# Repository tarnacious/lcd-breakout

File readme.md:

4 digit LCD Breakout board
==========================

This is a simple board to control a 4 digit reflexive LCD with three control
lines.

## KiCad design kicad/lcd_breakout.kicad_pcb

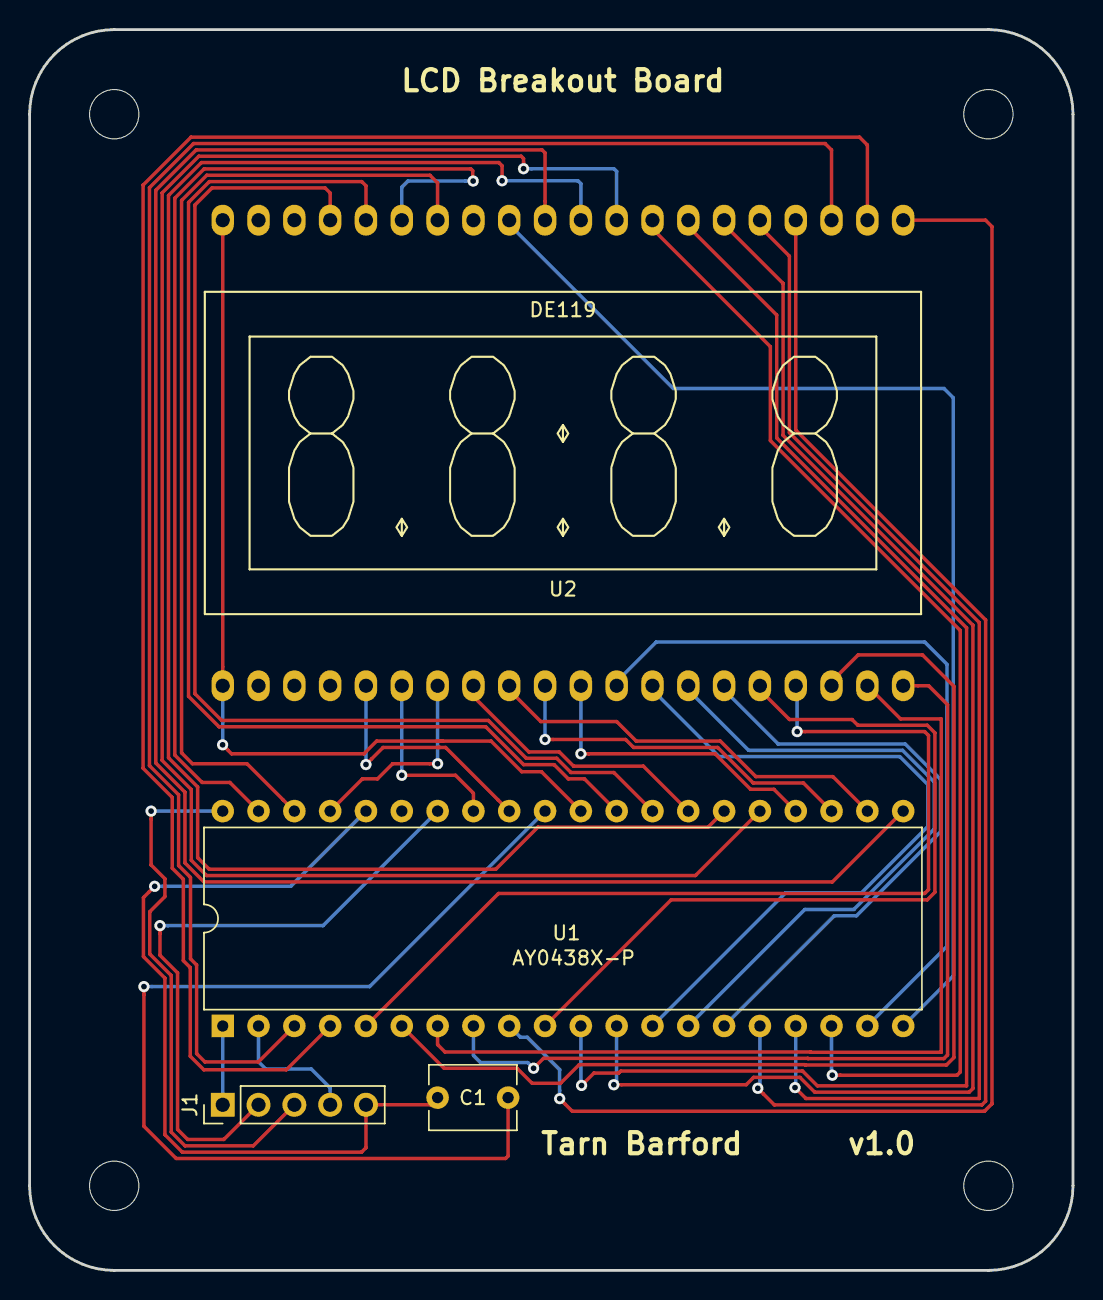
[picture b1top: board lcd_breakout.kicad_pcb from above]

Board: 2 copper layers, 74.0 x 88.0 mm, 4 parts (0 on the bottom side), 39 nets.

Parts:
C1: C 103; C_Disc_D6.0mm_W4.4mm_P5.00mm
J1: Conn_01x05_Male; PinHeader_1x05_P2.54mm_Vertical
U1: AY0438X-P; DIP-40_W15.24mm
U2: DE119

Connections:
GND: C1.1, J1.5, U1.36
unnamed: C1.2, U1.31
unnamed: J1.2, U1.34
unnamed: J1.3, U1.40
unnamed: J1.4, U1.2
unnamed: U1.3, U2.23
unnamed: U1.4, U2.22
unnamed: U1.5, U2.17
unnamed: U1.6, U2.18
unnamed: U1.7, U2.19
unnamed: U1.8, U2.20
unnamed: U1.9, U2.21
unnamed: U1.10, U2.16
unnamed: U1.11, U2.27
unnamed: U1.12, U2.26
unnamed: U1.13, U2.13
unnamed: U1.14, U2.14
unnamed: U1.15, U2.15
unnamed: U1.16, U2.24
unnamed: U1.17, U2.25
unnamed: U1.18, U2.28
unnamed: U1.19, U2.12
unnamed: U1.20, U2.32
unnamed: U1.21, U2.31
unnamed: U1.22, U2.9
unnamed: U1.23, U2.10
unnamed: U1.24, U2.11
unnamed: U1.25, U2.29
unnamed: U1.26, U2.30
unnamed: U1.27, U2.8
unnamed: U1.28, U2.37
unnamed: U1.29, U2.36
unnamed: U1.30, U2.1, U2.40
unnamed: U1.32, U2.5
unnamed: U1.33, U2.6
unnamed: U1.37, U2.7
unnamed: U1.38, U2.34
unnamed: U1.39, U2.35
VDD: J1.1, U1.1

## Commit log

2020-04-29 Add datasheets
2020-04-29 Add initial kicad files
2020-04-29 Update lcd component and schematic
2020-04-29 Add another datasheet for the lcd
2020-04-30 Add arduino driver code
2020-04-30 kicad adds schematics_editor section
2020-04-30 Add DE-119 footprint
2020-04-30 Start placing board
2020-05-07 Work on routing
2020-05-07 remove generated bak files
2020-05-07 ignore some generated files
2020-05-09 work on pcb layout
2020-05-10 pcb clean up for plotting
2020-05-10 add gerber files
2020-05-10 attempt to add some images in the readme
2020-05-10 error in schematic fixed
2020-05-10 update images and small clean up
2020-05-10 final update before getting v1 printed
2020-05-10 Update svg
2020-05-10 update gerber files
2020-05-22 show a countdown on a display
2020-05-22 add step file to import to freecad
